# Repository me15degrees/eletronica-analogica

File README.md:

## ELA I: Circuito de Teclado Musical com Transistores

Este projeto detalha a construção de um teclado musical de duas oitavas, concebido como parte da disciplina de Eletrônica Analógica Experimental 1. O circuito é composto por três estágios principais: um oscilador de relaxação, um amplificador de pequenos sinais e um amplificador de potência classe B em configuração push-pull.

### Etapas do Circuito

1.  **Oscilador de Relaxação:**
    O coração do teclado é um oscilador de relaxação que utiliza um transistor de unijunção (UTJ). A função deste estágio é gerar um sinal periódico (onda dente de serra) cuja frequência é determinada pela carga e descarga de um capacitor através de um resistor. A frequência do sinal, que corresponde às notas musicais, pode ser ajustada e é calculada teoricamente pela equação:

    $f_o \approx \frac{1.218}{RC}$

    Para a montagem, foi utilizado o transistor JFET modelo 2N2646.

2.  **Amplificador de Pequenos Sinais:**
    O sinal gerado pelo oscilador é então enviado para um amplificador de pequenos sinais. Este estágio emprega um transistor bipolar de junção (TBJ) com polarização por divisor de tensão. Sua finalidade é aumentar a tensão do sinal de entrada para que ele possa excitar o próximo estágio de forma adequada.

3.  **Amplificador de Potência (Push-Pull):**
    A etapa final consiste em um amplificador classe B, responsável por fornecer a corrente necessária para alimentar um alto-falante. Este amplificador é montado em uma configuração *push-pull*, com dois transistores (Q1 e Q2) que operam em seções simétricas para amplificar as partes positiva e negativa da onda do sinal de forma separada. Quando a tensão de entrada é positiva, o transistor Q1 conduz, enquanto o Q2 permanece em corte, e o inverso ocorre para tensões de entrada negativas. Os transistores utilizados nesta etapa são o BC337 (Q1) e o BC327 (Q2).

### Componentes Utilizados

| Estágio | Componente | Valor/Modelo |
| :--- | :--- | :--- |
| **Oscilador** | Transistor | JFET 2N2646 |
| | Capacitor (C) | 100 nF |
| | Resistores (RB1, RB2) | 1000 Ω, 100 Ω |
| **Amplificador de Pequenos Sinais** | Resistor (R1) | 5.6 kΩ |
| | Resistor (R2) | 1500 Ω |
| | Resistor (RC) | 330 Ω |
| | Resistor (RE) | 100 Ω |
| | Capacitor (C1) | 10 µF |
| | Capacitor (CE) | 10 µF |
| **Amplificador Push-Pull** | Transistor (Q1) | BC337 |
| | Transistor (Q2) | BC327 |
| | Diodos | IN4148 |
| | Resistor (R) | 4.7 kΩ |
| | Capacitor (CC) | 10 µF |

### Desenvolvimento da PCB e Montagem

Os esquemas elétricos e o layout da placa de circuito impresso (PCI) foram desenvolvidos com o software KiCad. A PCI foi confeccionada pelo método de termotransferência e corrosão com percloreto de ferro. A estrutura física do teclado, incluindo a *case* e as teclas, foi modelada em 3D com o software Tinkercad e impressa em uma impressora 3D. A alimentação do circuito é de 5V, podendo ser fornecida por um *power bank* ou uma fonte DC.

<div>
  align="center"

</div>

---

## ELA II: Amplificador Somador de Áudio com Reforçador de Corrente

Este projeto detalha a construção de um circuito eletrônico para mixagem e amplificação de dois canais de áudio (direito e esquerdo). O sistema utiliza um amplificador operacional na configuração de somador, seguido por um estágio reforçador de corrente para alimentar um alto-falante.

### Etapas do Circuito

1.  **Estágio de Entrada e Mixagem (Amplificador Somador):**
    O coração do circuito é o amplificador operacional NE5532 (U1), configurado como um amplificador somador inversor. Os sinais de áudio dos canais esquerdo (S) e direito (R), provenientes de um adaptador Bluetooth (J5), passam por capacitores de acoplamento (C3 e C4) para remover qualquer componente DC. Em seguida, os sinais são combinados nos resistores R1 e R2 e aplicados à entrada inversora (pino 2) do amplificador operacional. O resistor de feedback R3, em conjunto com R1 e R2, define o ganho de tensão do estágio. A entrada não-inversora (pino 3) é aterrada.

2.  **Estágio de Saída (Reforçador de Corrente Push-Pull):**
    O sinal amplificado na saída do NE5532 (pino 6) é enviado para um estágio de reforço de corrente. Este estágio utiliza um par de transistores de junção bipolar (BJT) em uma configuração *push-pull* classe B, composta por um transistor NPN (Q1) e um PNP (Q2). A função desta etapa é fornecer a corrente necessária para alimentar uma carga de baixa impedância, como o alto-falante (J3), sem sobrecarregar a saída do amplificador operacional. O transistor NPN amplifica o semiciclo positivo do sinal, enquanto o transistor PNP amplifica o semiciclo negativo.

3.  **Fonte de Alimentação:**
    O circuito é alimentado por uma fonte de +5V, conectada através de uma porta USB_A (J4). Essa tensão de entrada (+VCC) é então estabilizada pelo regulador de tensão U3. Os capacitores C1 e C2 são utilizados para filtrar ruídos na entrada e na saída do regulador, garantindo uma tensão de +5V estável para o circuito. As tensões de alimentação simétricas de +15V e -15V, indicadas no esquemático para alimentar o amplificador operacional, são representativas do modo de operação ideal do componente, mas o funcionamento prático do circuito depende da fonte conectada.

### Componentes Principais

| Componente | Referência | Função |
| :--- | :--- | :--- |
| Amplificador Operacional | U1 (NE5532) | Somar e amplificar os sinais de áudio de entrada. |
| Transistor NPN | Q1 | Amplificar o semiciclo positivo do sinal de áudio. |
| Transistor PNP | Q2 | Amplificar o semiciclo negativo do sinal de áudio. |
| Regulador de Tensão | U3 | Estabilizar a tensão de alimentação em +5V. |
| Conector de Entrada | J5 | Interface para o adaptador Bluetooth. |
| Conector de Saída | J3 | Conexão para o alto-falante. |
| Conector de Alimentação | J4 (USB_A) | Ponto de entrada da alimentação de +5V. |
| Resistores | R1, R2 (10kΩ) | Resistores de entrada do somador. |
| Resistor | R3 (10kΩ) | Resistor de feedback, define o ganho. |
| Capacitores | C3, C4 (10µF) | Capacitores de acoplamento para os canais de áudio. |
| Capacitores | C1, C2 (100µF) | Capacitores de filtro para o regulador de tensão. |

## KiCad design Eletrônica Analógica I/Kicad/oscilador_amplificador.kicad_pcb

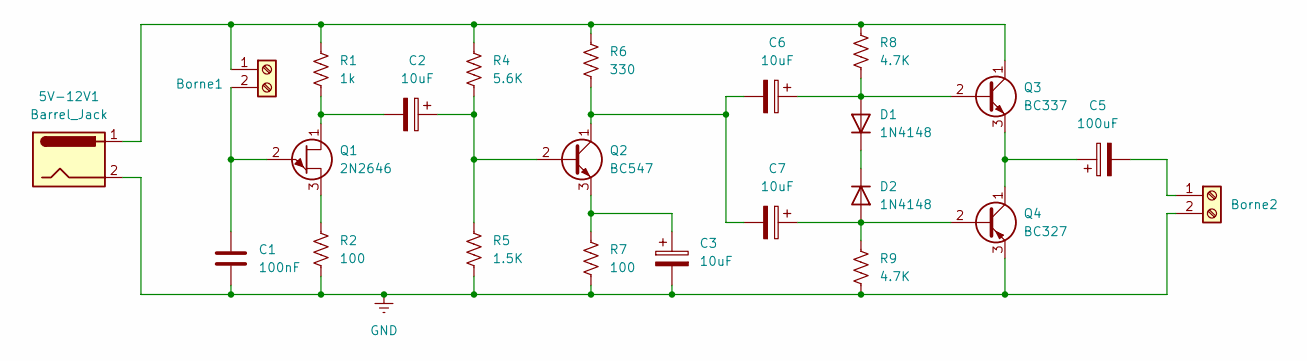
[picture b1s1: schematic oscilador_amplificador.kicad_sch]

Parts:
5V-12V1: Barrel_Jack; BarrelJack_SwitchcraftConxall_RAPC10U_Horizontal
C1: 100nF; C_Radial_D8.0mm_H11.5mm_P3.50mm
C2, C3, C6, C7: 10uF; C_Radial_D5.0mm_H11.0mm_P2.00mm
C5: 100uF; C_Radial_D8.0mm_H11.5mm_P3.50mm
D1, D2: 1N4148; D_DO-35_SOD27_P7.62mm_Horizontal
J1: Borne1; TerminalBlock_bornier-2_P5.08mm
J3: Borne2; TerminalBlock_bornier-2_P5.08mm
Q1: 2N2646; TO-18-3
Q2: BC547; TO-92_Inline
Q3: BC337; TO-92_Inline
Q4: BC327; TO-92_Inline
R1: 1k; R_Axial_DIN0207_L6.3mm_D2.5mm_P7.62mm_Horizontal
R2, R7: 100; R_Axial_DIN0207_L6.3mm_D2.5mm_P7.62mm_Horizontal
R4: 5.6K; R_Axial_DIN0207_L6.3mm_D2.5mm_P7.62mm_Horizontal
R5: 1.5K; R_Axial_DIN0207_L6.3mm_D2.5mm_P7.62mm_Horizontal
R6: 330; R_Axial_DIN0207_L6.3mm_D2.5mm_P7.62mm_Horizontal
R8, R9: 4.7K; R_Axial_DIN0207_L6.3mm_D2.5mm_P7.62mm_Horizontal

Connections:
GND: 5V-12V1.2, C1.2, C3.2, J3.2, Q4.3 (E), R2.2, R5.2, R7.2, R9.2
unnamed: C6.1, D1.2 (A), Q3.2 (B), R8.2
unnamed: D1.1 (K), D2.1 (K)
unnamed: C7.1, D2.2 (A), Q4.2 (B), R9.1
unnamed: 5V-12V1.1, J1.1, Q3.1 (C), R1.1, R4.1, R6.1, R8.1
unnamed: C1.1, J1.2, Q1.2 (E)
unnamed: C5.2, J3.1
unnamed: Q1.3 (B1), R2.1
unnamed: C2.2, Q1.1 (B2), R1.2
unnamed: C2.1, Q2.2 (B), R4.2, R5.1
unnamed: C6.2, C7.2, Q2.1 (C), R6.2
unnamed: C3.1, Q2.3 (E), R7.1
unnamed: C5.1, Q3.3 (E), Q4.1 (C)

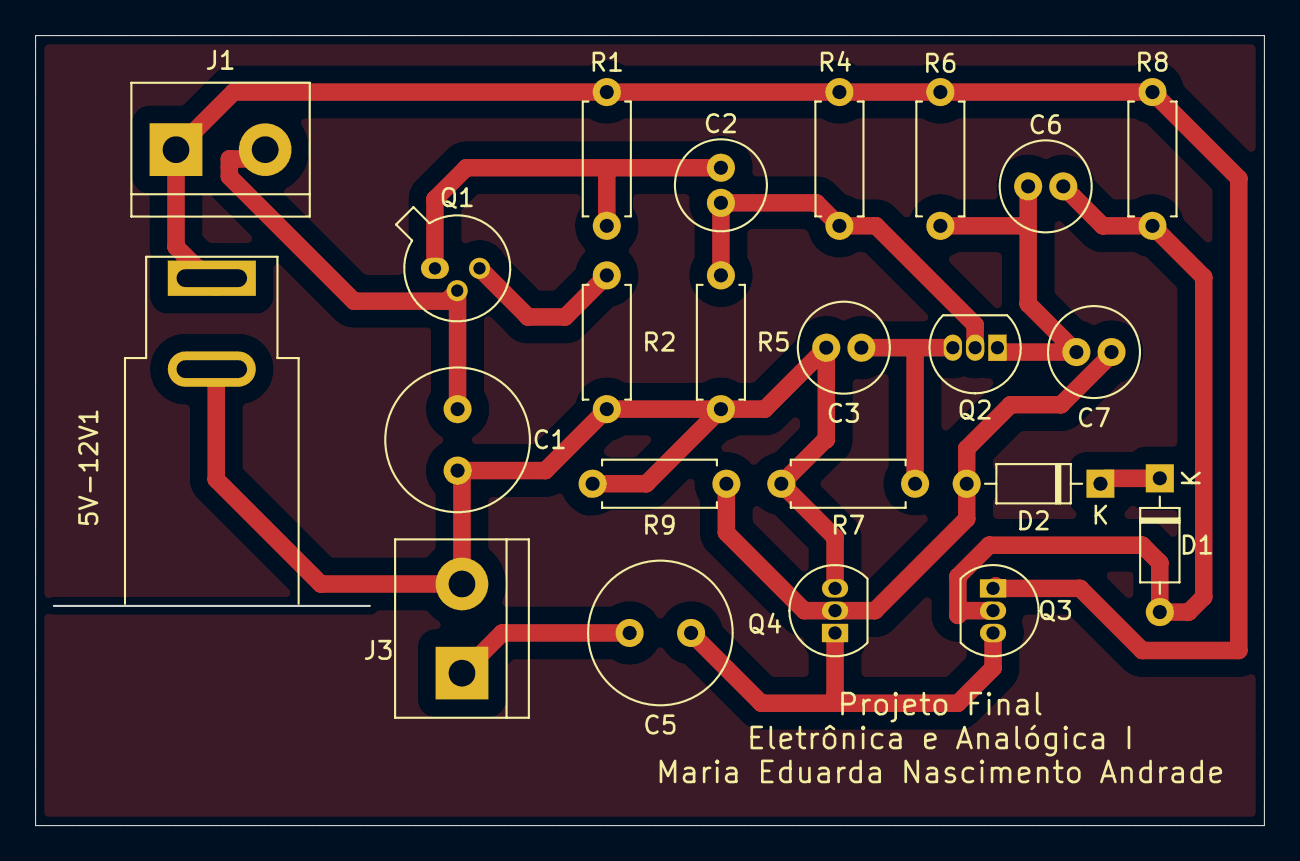
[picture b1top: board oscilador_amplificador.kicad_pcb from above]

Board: 2 copper layers, 69.9 x 44.9 mm, 23 parts (0 on the bottom side), 13 nets.

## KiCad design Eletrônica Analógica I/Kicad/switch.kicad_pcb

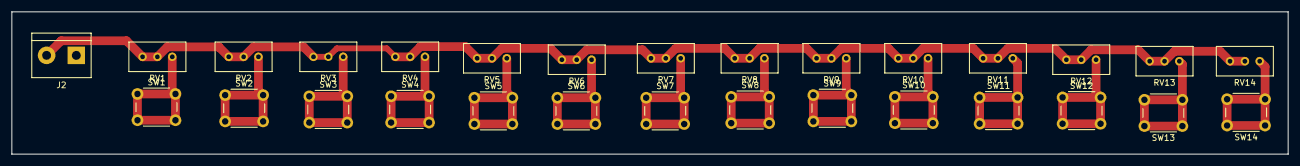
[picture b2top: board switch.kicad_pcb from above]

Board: 2 copper layers, 218.4 x 24.4 mm, 29 parts (0 on the bottom side), 15 nets.

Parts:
J2: Screw_Terminal_01x02; TerminalBlock_bornier-2_P5.08mm
RV1, RV2, RV3, RV4, RV5, RV6, RV7, RV8, RV9, RV10, RV11, RV12, RV13, RV14: R_Potentiometer_Trim_US; Potentiometer_Bourns_3296W_Vertical
SW1, SW2, SW3, SW4, SW5, SW6, SW7, SW8, SW9, SW10, SW11, SW12, SW13, SW14: SW_Push; SW_PUSH_6mm_H4.3mm

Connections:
unnamed: J2.2, RV1.1, RV1.2, RV2.1, RV2.2, RV3.1, RV3.2, RV4.1, RV4.2, RV5.1, RV5.2, RV6.1, RV6.2, RV7.1, RV7.2, RV8.1, RV8.2, RV9.1, RV9.2, RV10.1, RV10.2, RV11.1, RV11.2, RV12.1, RV12.2, RV13.1, RV13.2, RV14.1, RV14.2
unnamed: RV1.3, SW1.1 (A), SW1.2 (A)
unnamed: RV2.3, SW2.1 (A), SW2.2 (A)
unnamed: RV3.3, SW3.1 (A), SW3.2 (A)
unnamed: RV4.3, SW4.1 (A), SW4.2 (A)
unnamed: RV5.3, SW5.1 (A), SW5.2 (A)
unnamed: RV6.3, SW6.1 (A), SW6.2 (A)
unnamed: RV7.3, SW7.1 (A), SW7.2 (A)
unnamed: RV8.3, SW8.1 (A), SW8.2 (A)
unnamed: RV9.3, SW9.1 (A), SW9.2 (A)
unnamed: RV10.3, SW10.1 (A), SW10.2 (A)
unnamed: RV11.3, SW11.1 (A), SW11.2 (A)
unnamed: RV12.3, SW12.1 (A), SW12.2 (A)
unnamed: RV13.3, SW13.1 (A), SW13.2 (A)
unnamed: RV14.3, SW14.1 (A), SW14.2 (A)

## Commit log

2025-09-25 add: kicad files
2025-09-25 create: README.md
